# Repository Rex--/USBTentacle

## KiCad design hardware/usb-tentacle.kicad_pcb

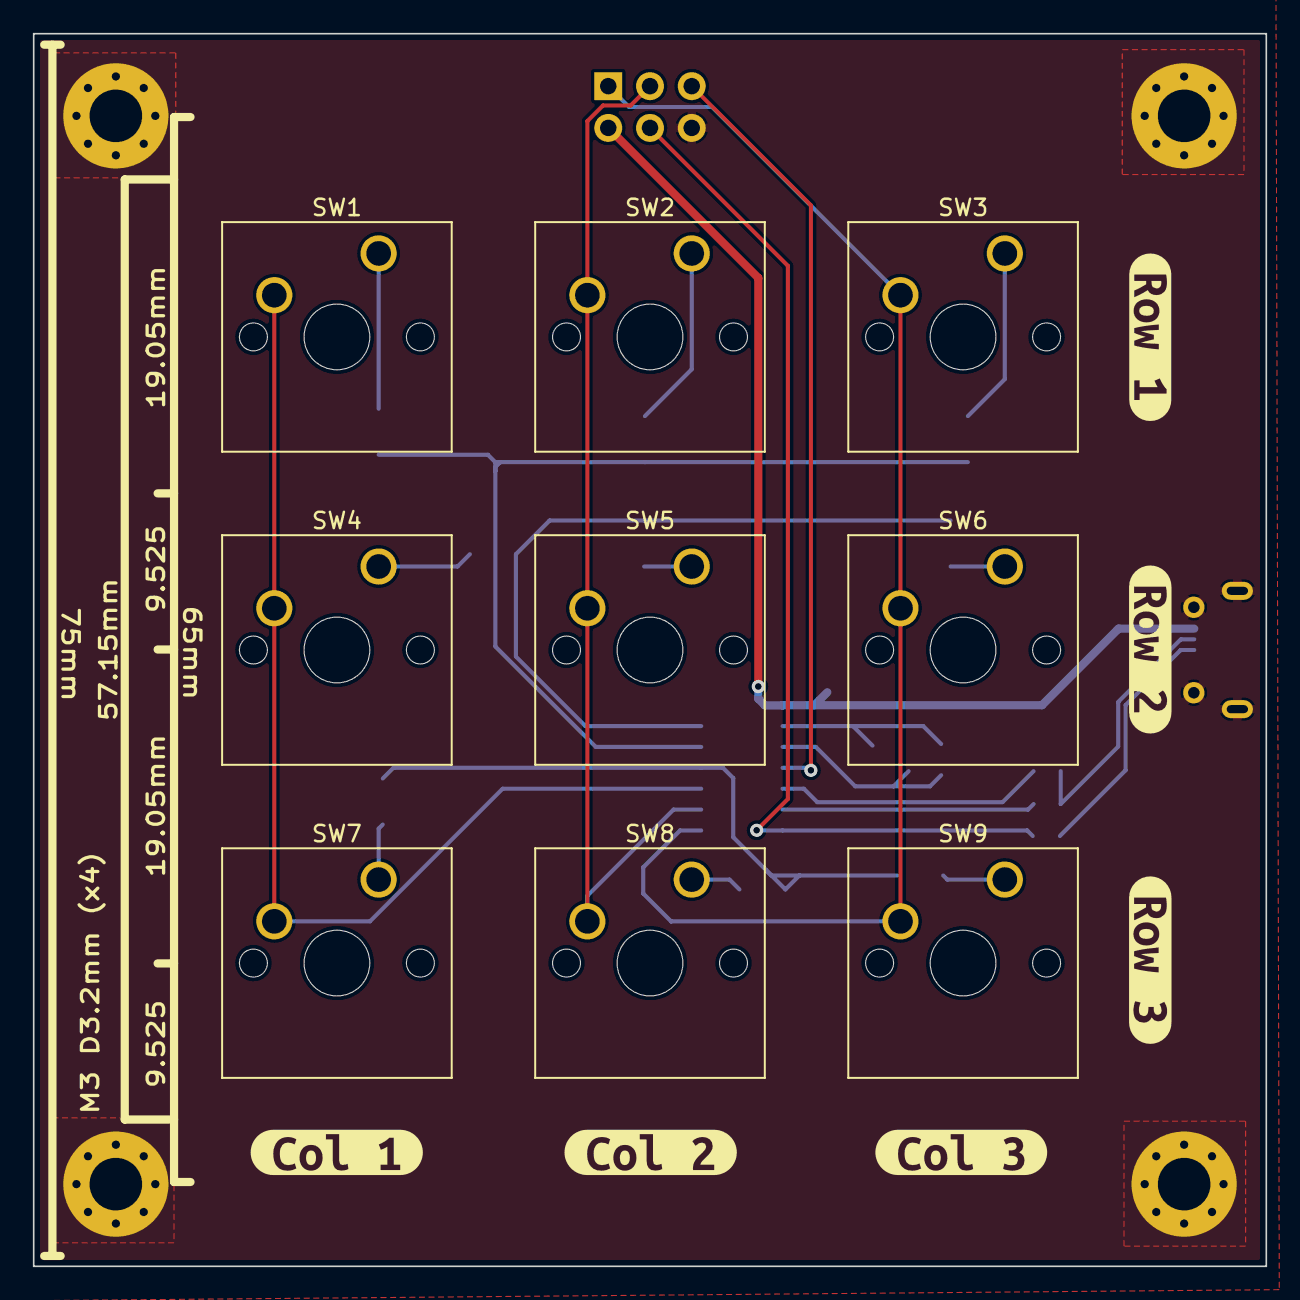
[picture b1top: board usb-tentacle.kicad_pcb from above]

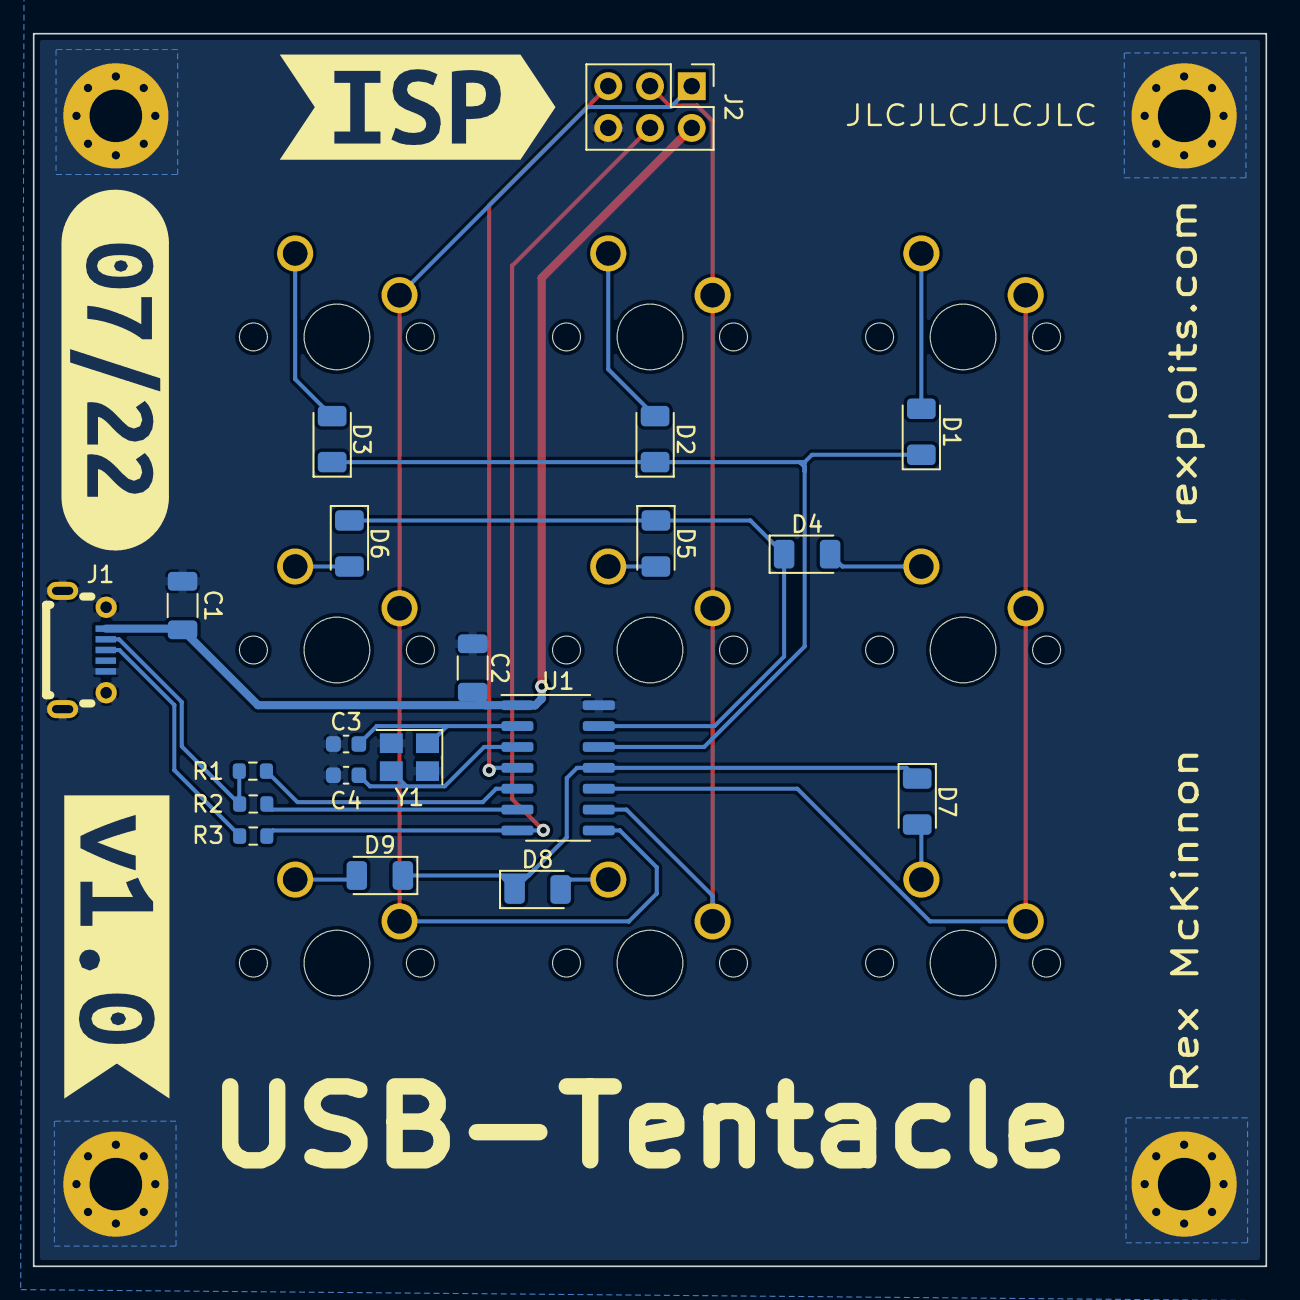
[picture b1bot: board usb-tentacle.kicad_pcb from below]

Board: 2 copper layers, 75.0 x 75.0 mm, 38 parts (23 on the bottom side), 25 nets.

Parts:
C1: 1uF; C_1206_3216Metric
C2: 0.1uF; C_1206_3216Metric
C3, C4: TBD; C_0603_1608Metric
D1, D2, D3, D4, D5, D6, D7, D8, D9: D; D_1206_3216Metric
J1: USB_B_Micro; USB_Micro-B_Receptacle_AdamTech_MCR-B-S-RA-SMT-CS5A-NF-TR
J2: AVR-ISP-6; PinHeader_2x03_P2.54mm_Vertical
R1: 1.5K; R_0603_1608Metric
R2, R3: 680; R_0603_1608Metric
SW1, SW2, SW3, SW4, SW5, SW6, SW7, SW8, SW9: SW_Push; SW_Cherry_MX_1.00u_PCB
U1: ATtiny44A-SS; SOIC-14_3.9x8.7mm_P1.27mm
Y1: 12MHz; Crystal_SMD_3225-4Pin_3.2x2.5mm
kibuzzard-62D88EEF: G***; kibuzzard-62D88EEF
kibuzzard-62D88F2B: G***; kibuzzard-62D88F2B
kibuzzard-62D88F18: G***; kibuzzard-62D88F18
kibuzzard-62D88F66: G***; kibuzzard-62D88F66
kibuzzard-62D88F76: G***; kibuzzard-62D88F76
kibuzzard-62D88F88: G***; kibuzzard-62D88F88
kibuzzard-62D873FF: G***; kibuzzard-62D873FF
kibuzzard-62D87485: G***; kibuzzard-62D87485
kibuzzard-62D87684: G***; kibuzzard-62D87684

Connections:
/COL_1: SW1.2, SW4.2, SW7.2, U1.10 (PA3)
/COL_2: J2.3 (SCK), SW2.2, SW5.2, SW8.2, U1.9 (PA4)
/COL_3: J2.1 (MISO), SW3.2, SW6.2, SW9.2, U1.8 (PA5)
/D+: J2.4 (MOSI), R3.1, U1.7 (PA6)
/D-: R2.1, U1.6 (PA7)
/PUD-: R1.2, U1.5 (PB2)
/ROW_1: D1.1 (K), D2.1 (K), D3.1 (K), U1.12 (PA1)
/ROW_2: D4.1 (K), D5.1 (K), D6.1 (K), U1.13 (AREF/PA0)
/ROW_3: D7.1 (K), D8.1 (K), D9.1 (K), U1.11 (PA2)
GND: C1.2, C2.2, C3.2, C4.2, J1.5 (GND), J1.6 (Shield), J2.6 (GND), U1.14 (GND), Y1.2, Y1.4
unnamed: C4.1, U1.3 (XTAL2/PB1), Y1.3
unnamed: D1.2 (A), SW1.1
unnamed: D2.2 (A), SW2.1
unnamed: D3.2 (A), SW3.1
unnamed: D4.2 (A), SW4.1
unnamed: D5.2 (A), SW5.1
unnamed: D6.2 (A), SW6.1
unnamed: D7.2 (A), SW7.1
unnamed: D8.2 (A), SW8.1
unnamed: D9.2 (A), SW9.1
unnamed: J1.2 (D-), R1.1, R2.2
unnamed: J1.3 (D+), R3.2
unnamed: C3.1, U1.2 (XTAL1/PB0), Y1.1
unnamed: J2.5 (~RST), U1.4 (~RESET/PB3)
VBUS: C1.1, C2.1, J1.1 (VBUS), J2.2 (VCC), U1.1 (VCC)

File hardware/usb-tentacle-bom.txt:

################################################################################
#                                                                              #
#                     USB-Tentacle v1.0 Bill of Materials                      #
#                                                                              #
################################################################################
#          #                    #                                              #
#   Ref    #       Value        #            Part Number / Footprint           #
#          #                    #                                              #
################################################################################
|----------|--------------------|----------------------------------------------|
|    C1    |        1uF         |                     1206                     |
|----------|--------------------|----------------------------------------------|
|    C2    |       0.1uF        |                     1206                     |
|----------|--------------------|----------------------------------------------|
|  C3, C4  |        TBD         |                     0603                     |
|----------|--------------------|----------------------------------------------|
|D1, D2, ..|      Schotty       |                SD1206S040S0R5                |
|----------|--------------------|----------------------------------------------|
|    J1    |    USB B Micro     |          MCR-B-S-RA-SMT-CS5A-NF-T/R          |
|----------|--------------------|----------------------------------------------|
|    J2    |     AVR-ISP-6      |             2x3 Male Pin Header              |
|----------|--------------------|----------------------------------------------|
|    R1    |        1.5K        |                     0603                     |
|----------|--------------------|----------------------------------------------|
|  R2, R3  |        680         |                     0603                     |
|----------|--------------------|----------------------------------------------|
|SW1, SW2..|        Push        |             Cherry MX Keyswitch              |
|----------|--------------------|----------------------------------------------|
|    U1    |    ATtiny44A-SS    |                ATTINY44A-SSN                 |
|----------|--------------------|----------------------------------------------|
|    Y1    |       12MHz        |            ECS-120-20-33-ckm-tr3             |
|----------|--------------------|----------------------------------------------|
################################################################################
         Generated at Fri 12 Aug 2022 04:39:54 PM PDT by kicad-bom-gen

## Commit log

2024-03-24 Inital version
